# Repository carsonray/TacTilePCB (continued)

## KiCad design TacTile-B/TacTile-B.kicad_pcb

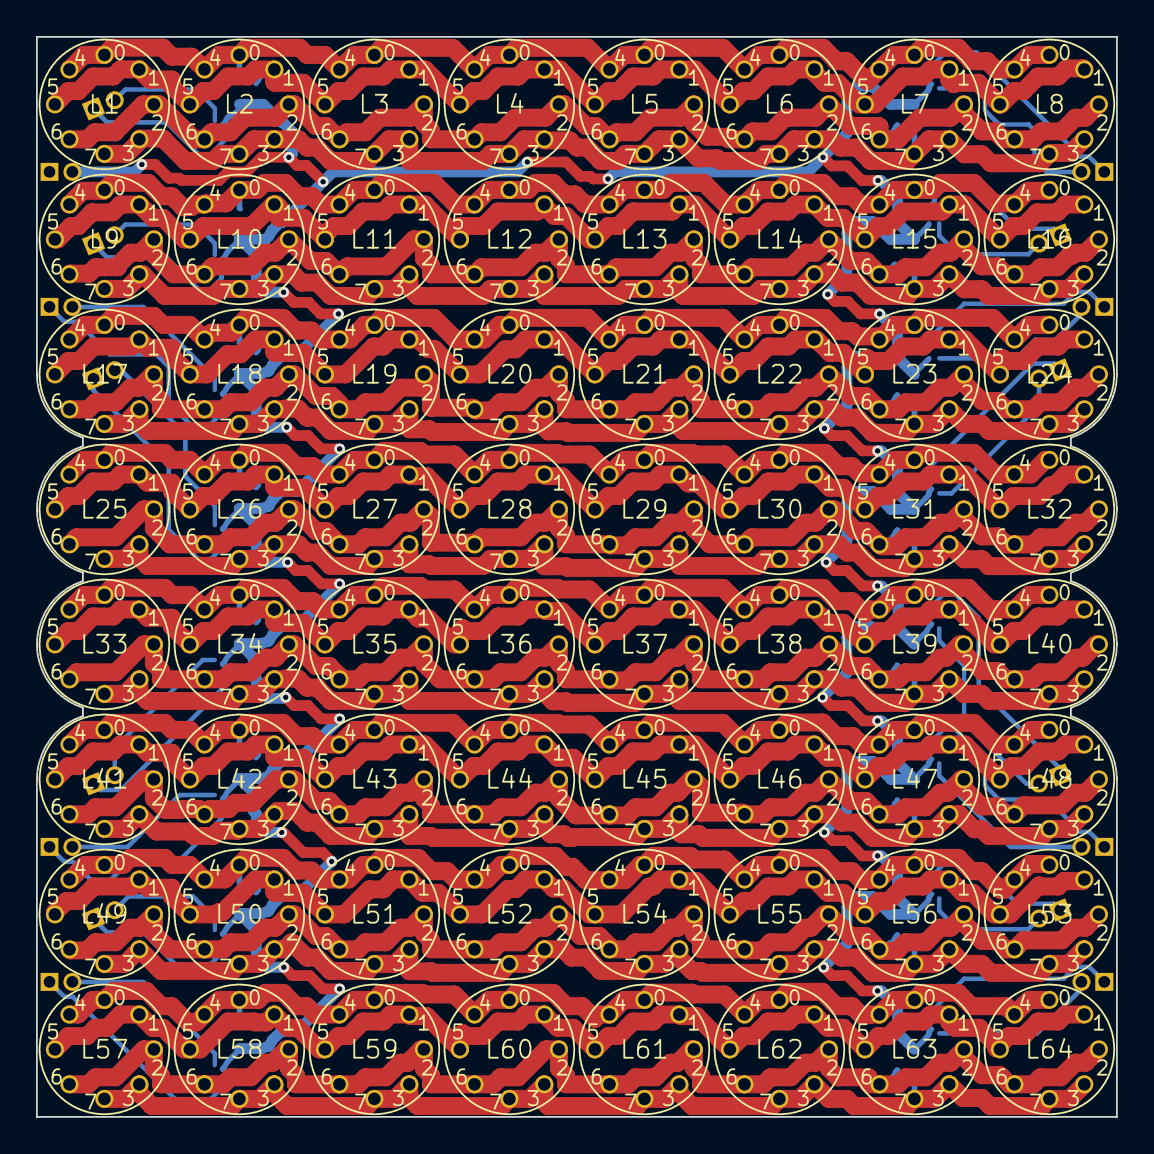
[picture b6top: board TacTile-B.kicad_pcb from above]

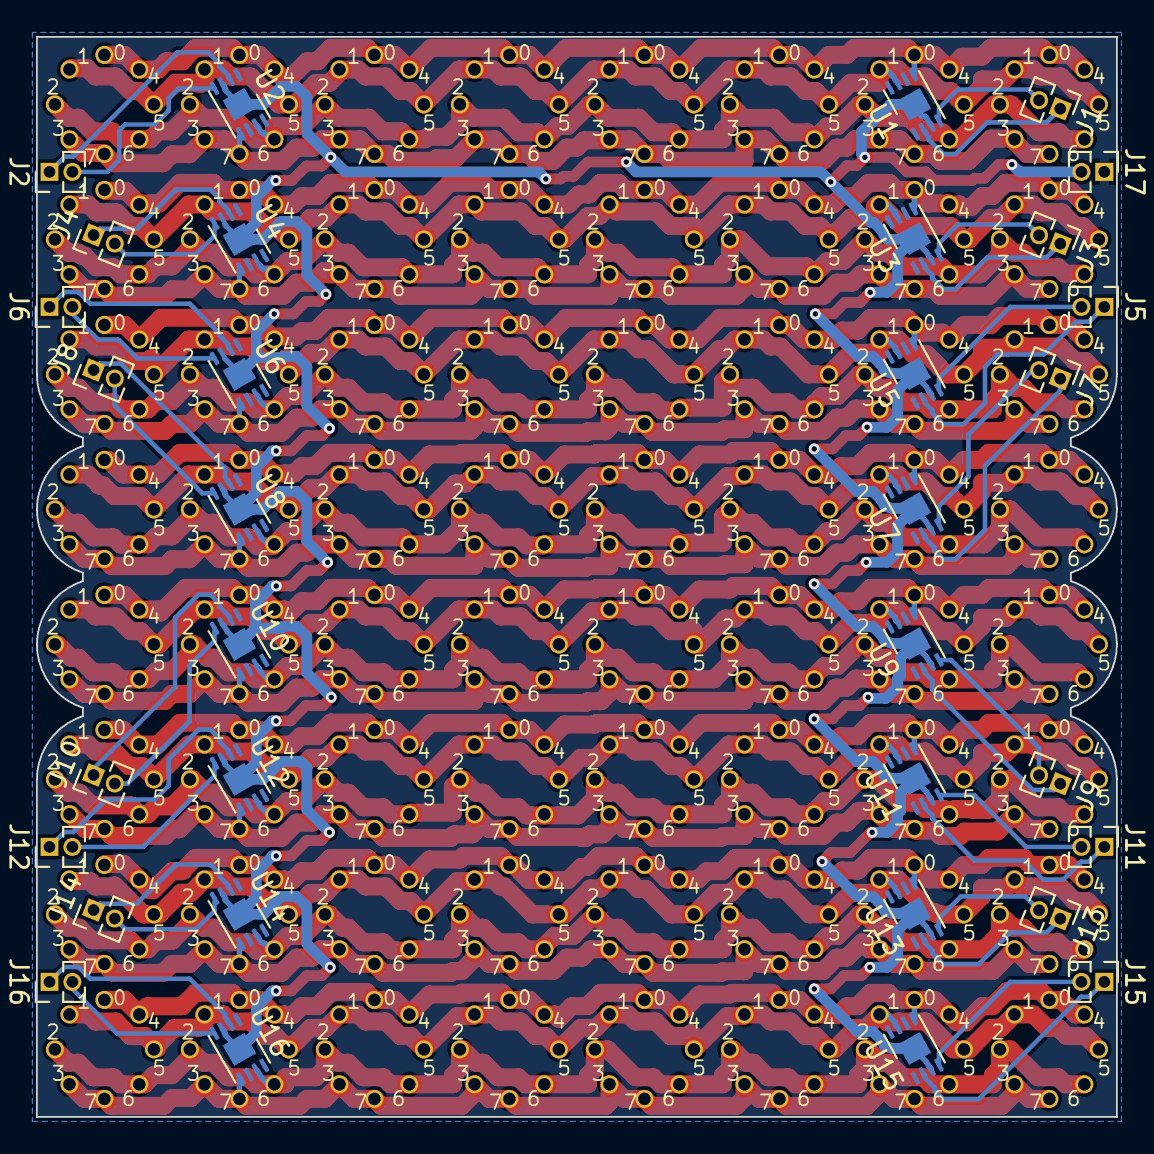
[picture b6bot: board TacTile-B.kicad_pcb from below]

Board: 2 copper layers, 60.0 x 60.0 mm, 97 parts (33 on the bottom side), 66 nets.

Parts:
J1, J2, J3, J4, J5, J6, J7, J8, J9, J10, J11, J12, J13, J14, J15, J16, J17: Conn_01x02; PinHeader_1x02_P1.27mm_Vertical
L1, L2, L3, L4, L5, L6, L7, L8, L9, L10, L11, L12, L13, L14, L15, L16, L17, L18, L19, L20, L21, L22, L23, L24, L25, L26, L27, L28, L29, L30, L31, L32, L33, L34, L35, L36, L37, L38, L39, L40, L41, L42, L43, L44, L45, L46, L47, L48, L49, L50, L51, L52, L53, L54, L55, L56, L57, L58, L59, L60, L61, L62, L63, L64: 8_coil_solenoid; 8_coil_solenoid_SMD
U1, U2, U3, U4, U5, U6, U7, U8, U9, U10, U11, U12, U13, U14, U15, U16: MCP14A0304xMNY; WDFN-8-1EP_3x2mm_P0.5mm_EP1.3x1.4mm

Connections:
/GND: J17.2, U1.3 (GND), U1.9 (GND), U2.3 (GND), U2.9 (GND), U3.3 (GND), U3.9 (GND), U4.3 (GND), U4.9 (GND), U5.3 (GND), U5.9 (GND), U6.3 (GND), U6.9 (GND), U7.3 (GND), U7.9 (GND), U8.3 (GND), U8.9 (GND), U9.3 (GND), U9.9 (GND), U10.3 (GND), U10.9 (GND), U11.3 (GND), U11.9 (GND), U12.3 (GND), U12.9 (GND), U13.3 (GND), U13.9 (GND), U14.3 (GND), U14.9 (GND), U15.3 (GND), U15.9 (GND), U16.3 (GND), U16.9 (GND)
/INP0: J1.2, U1.4 (INB)
/INP1: J1.1, U1.2 (INA)
/INP2: J2.1, U2.2 (INA)
/INP3: J2.2, U2.4 (INB)
/INP4: J3.2, U3.4 (INB)
/INP5: J3.1, U3.2 (INA)
/INP6: J4.1, U4.2 (INA)
/INP7: J4.2, U4.4 (INB)
/INP8: J5.2, U5.4 (INB)
/INP9: J5.1, U5.2 (INA)
/INP10: J6.1, U6.2 (INA)
/INP11: J6.2, U6.4 (INB)
/INP12: J7.2, U7.4 (INB)
/INP13: J7.1, U7.2 (INA)
/INP14: J8.1, U8.2 (INA)
/INP15: J8.2, U8.4 (INB)
/INP16: J9.2, U9.4 (INB)
/INP17: J9.1, U9.2 (INA)
/INP18: J10.1, U10.2 (INA)
/INP19: J10.2, U10.4 (INB)
/INP20: J11.2, U11.4 (INB)
/INP21: J11.1, U11.2 (INA)
/INP22: J12.1, U12.2 (INA)
/INP23: J12.2, U12.4 (INB)
/INP24: J13.2, U13.4 (INB)
/INP25: J13.1, U13.2 (INA)
/INP26: J14.1, U14.2 (INA)
/INP27: J14.2, U14.4 (INB)
/INP28: J15.2, U15.4 (INB)
/INP29: J15.1, U15.2 (INA)
/INP30: J16.1, U16.2 (INA)
/INP31: J16.2, U16.4 (INB)
/VIN: J17.1, U1.6 (V+), U2.6 (V+), U3.6 (V+), U4.6 (V+), U5.6 (V+), U6.6 (V+), U7.6 (V+), U8.6 (V+), U9.6 (V+), U10.6 (V+), U11.6 (V+), U12.6 (V+), U13.6 (V+), U14.6 (V+), U15.6 (V+), U16.6 (V+)
/VIN0: L1.1 (A), L1.5 (A), L2.1 (A), L2.5 (A), L3.1 (A), L3.5 (A), L4.1 (A), L4.5 (A), L5.1 (A), L5.5 (A), L6.1 (A), L6.5 (A), L7.1 (A), L7.5 (A), L8.1 (A), L8.5 (A), U1.5 (OUTB)
/VIN1: L1.2 (A), L1.6 (A), L2.2 (A), L2.6 (A), L3.2 (A), L3.6 (A), L4.2 (A), L4.6 (A), L5.2 (A), L5.6 (A), L6.2 (A), L6.6 (A), L7.2 (A), L7.6 (A), L8.2 (A), L8.6 (A), U1.7 (OUTA)
/VIN2: L1.3 (A), L1.7 (A), L2.3 (A), L2.7 (A), L3.3 (A), L3.7 (A), L4.3 (A), L4.7 (A), L5.3 (A), L5.7 (A), L6.3 (A), L6.7 (A), L7.3 (A), L7.7 (A), L8.3 (A), L8.7 (A), U2.7 (OUTA)
/VIN3: L1.4 (A), L1.8 (A), L2.4 (A), L2.8 (A), L3.4 (A), L3.8 (A), L4.4 (A), L4.8 (A), L5.4 (A), L5.8 (A), L6.4 (A), L6.8 (A), L7.4 (A), L7.8 (A), L8.4 (A), L8.8 (A), U2.5 (OUTB)
/VIN4: L9.1 (A), L9.5 (A), L10.1 (A), L10.5 (A), L11.1 (A), L11.5 (A), L12.1 (A), L12.5 (A), L13.1 (A), L13.5 (A), L14.1 (A), L14.5 (A), L15.1 (A), L15.5 (A), L16.1 (A), L16.5 (A), U3.5 (OUTB)
/VIN5: L9.2 (A), L9.6 (A), L10.2 (A), L10.6 (A), L11.2 (A), L11.6 (A), L12.2 (A), L12.6 (A), L13.2 (A), L13.6 (A), L14.2 (A), L14.6 (A), L15.2 (A), L15.6 (A), L16.2 (A), L16.6 (A), U3.7 (OUTA)
/VIN6: L9.3 (A), L9.7 (A), L10.3 (A), L10.7 (A), L11.3 (A), L11.7 (A), L12.3 (A), L12.7 (A), L13.3 (A), L13.7 (A), L14.3 (A), L14.7 (A), L15.3 (A), L15.7 (A), L16.3 (A), L16.7 (A), U4.7 (OUTA)
/VIN7: L9.4 (A), L9.8 (A), L10.4 (A), L10.8 (A), L11.4 (A), L11.8 (A), L12.4 (A), L12.8 (A), L13.4 (A), L13.8 (A), L14.4 (A), L14.8 (A), L15.4 (A), L15.8 (A), L16.4 (A), L16.8 (A), U4.5 (OUTB)
/VIN8: L17.1 (A), L17.5 (A), L18.1 (A), L18.5 (A), L19.1 (A), L19.5 (A), L20.1 (A), L20.5 (A), L21.1 (A), L21.5 (A), L22.1 (A), L22.5 (A), L23.1 (A), L23.5 (A), L24.1 (A), L24.5 (A), U5.5 (OUTB)
/VIN9: L17.2 (A), L17.6 (A), L18.2 (A), L18.6 (A), L19.2 (A), L19.6 (A), L20.2 (A), L20.6 (A), L21.2 (A), L21.6 (A), L22.2 (A), L22.6 (A), L23.2 (A), L23.6 (A), L24.2 (A), L24.6 (A), U5.7 (OUTA)
/VIN10: L17.3 (A), L17.7 (A), L18.3 (A), L18.7 (A), L19.3 (A), L19.7 (A), L20.3 (A), L20.7 (A), L21.3 (A), L21.7 (A), L22.3 (A), L22.7 (A), L23.3 (A), L23.7 (A), L24.3 (A), L24.7 (A), U6.7 (OUTA)
/VIN11: L17.4 (A), L17.8 (A), L18.4 (A), L18.8 (A), L19.4 (A), L19.8 (A), L20.4 (A), L20.8 (A), L21.4 (A), L21.8 (A), L22.4 (A), L22.8 (A), L23.4 (A), L23.8 (A), L24.4 (A), L24.8 (A), U6.5 (OUTB)
/VIN12: L25.1 (A), L25.5 (A), L26.1 (A), L26.5 (A), L27.1 (A), L27.5 (A), L28.1 (A), L28.5 (A), L29.1 (A), L29.5 (A), L30.1 (A), L30.5 (A), L31.1 (A), L31.5 (A), L32.1 (A), L32.5 (A), U7.5 (OUTB)
/VIN13: L25.2 (A), L25.6 (A), L26.2 (A), L26.6 (A), L27.2 (A), L27.6 (A), L28.2 (A), L28.6 (A), L29.2 (A), L29.6 (A), L30.2 (A), L30.6 (A), L31.2 (A), L31.6 (A), L32.2 (A), L32.6 (A), U7.7 (OUTA)
/VIN14: L25.3 (A), L25.7 (A), L26.3 (A), L26.7 (A), L27.3 (A), L27.7 (A), L28.3 (A), L28.7 (A), L29.3 (A), L29.7 (A), L30.3 (A), L30.7 (A), L31.3 (A), L31.7 (A), L32.3 (A), L32.7 (A), U8.7 (OUTA)
/VIN15: L25.4 (A), L25.8 (A), L26.4 (A), L26.8 (A), L27.4 (A), L27.8 (A), L28.4 (A), L28.8 (A), L29.4 (A), L29.8 (A), L30.4 (A), L30.8 (A), L31.4 (A), L31.8 (A), L32.4 (A), L32.8 (A), U8.5 (OUTB)
/VIN16: L33.1 (A), L33.5 (A), L34.1 (A), L34.5 (A), L35.1 (A), L35.5 (A), L36.1 (A), L36.5 (A), L37.1 (A), L37.5 (A), L38.1 (A), L38.5 (A), L39.1 (A), L39.5 (A), L40.1 (A), L40.5 (A), U9.5 (OUTB)
/VIN17: L33.2 (A), L33.6 (A), L34.2 (A), L34.6 (A), L35.2 (A), L35.6 (A), L36.2 (A), L36.6 (A), L37.2 (A), L37.6 (A), L38.2 (A), L38.6 (A), L39.2 (A), L39.6 (A), L40.2 (A), L40.6 (A), U9.7 (OUTA)
/VIN18: L33.3 (A), L33.7 (A), L34.3 (A), L34.7 (A), L35.3 (A), L35.7 (A), L36.3 (A), L36.7 (A), L37.3 (A), L37.7 (A), L38.3 (A), L38.7 (A), L39.3 (A), L39.7 (A), L40.3 (A), L40.7 (A), U10.7 (OUTA)
/VIN19: L33.4 (A), L33.8 (A), L34.4 (A), L34.8 (A), L35.4 (A), L35.8 (A), L36.4 (A), L36.8 (A), L37.4 (A), L37.8 (A), L38.4 (A), L38.8 (A), L39.4 (A), L39.8 (A), L40.4 (A), L40.8 (A), U10.5 (OUTB)
/VIN20: L41.1 (A), L41.5 (A), L42.1 (A), L42.5 (A), L43.1 (A), L43.5 (A), L44.1 (A), L44.5 (A), L45.1 (A), L45.5 (A), L46.1 (A), L46.5 (A), L47.1 (A), L47.5 (A), L48.1 (A), L48.5 (A), U11.5 (OUTB)
/VIN21: L41.2 (A), L41.6 (A), L42.2 (A), L42.6 (A), L43.2 (A), L43.6 (A), L44.2 (A), L44.6 (A), L45.2 (A), L45.6 (A), L46.2 (A), L46.6 (A), L47.2 (A), L47.6 (A), L48.2 (A), L48.6 (A), U11.7 (OUTA)
/VIN22: L41.3 (A), L41.7 (A), L42.3 (A), L42.7 (A), L43.3 (A), L43.7 (A), L44.3 (A), L44.7 (A), L45.3 (A), L45.7 (A), L46.3 (A), L46.7 (A), L47.3 (A), L47.7 (A), L48.3 (A), L48.7 (A), U12.7 (OUTA)
/VIN23: L41.4 (A), L41.8 (A), L42.4 (A), L42.8 (A), L43.4 (A), L43.8 (A), L44.4 (A), L44.8 (A), L45.4 (A), L45.8 (A), L46.4 (A), L46.8 (A), L47.4 (A), L47.8 (A), L48.4 (A), L48.8 (A), U12.5 (OUTB)
/VIN24: L49.1 (A), L49.5 (A), L50.1 (A), L50.5 (A), L51.1 (A), L51.5 (A), L52.1 (A), L52.5 (A), L53.1 (A), L53.5 (A), L54.1 (A), L54.5 (A), L55.1 (A), L55.5 (A), L56.1 (A), L56.5 (A), U13.5 (OUTB)
/VIN25: L49.2 (A), L49.6 (A), L50.2 (A), L50.6 (A), L51.2 (A), L51.6 (A), L52.2 (A), L52.6 (A), L53.2 (A), L53.6 (A), L54.2 (A), L54.6 (A), L55.2 (A), L55.6 (A), L56.2 (A), L56.6 (A), U13.7 (OUTA)
/VIN26: L49.3 (A), L49.7 (A), L50.3 (A), L50.7 (A), L51.3 (A), L51.7 (A), L52.3 (A), L52.7 (A), L53.3 (A), L53.7 (A), L54.3 (A), L54.7 (A), L55.3 (A), L55.7 (A), L56.3 (A), L56.7 (A), U14.7 (OUTA)
/VIN27: L49.4 (A), L49.8 (A), L50.4 (A), L50.8 (A), L51.4 (A), L51.8 (A), L52.4 (A), L52.8 (A), L53.4 (A), L53.8 (A), L54.4 (A), L54.8 (A), L55.4 (A), L55.8 (A), L56.4 (A), L56.8 (A), U14.5 (OUTB)
/VIN28: L57.1 (A), L57.5 (A), L58.1 (A), L58.5 (A), L59.1 (A), L59.5 (A), L60.1 (A), L60.5 (A), L61.1 (A), L61.5 (A), L62.1 (A), L62.5 (A), L63.1 (A), L63.5 (A), L64.1 (A), L64.5 (A), U15.5 (OUTB)
/VIN29: L57.2 (A), L57.6 (A), L58.2 (A), L58.6 (A), L59.2 (A), L59.6 (A), L60.2 (A), L60.6 (A), L61.2 (A), L61.6 (A), L62.2 (A), L62.6 (A), L63.2 (A), L63.6 (A), L64.2 (A), L64.6 (A), U15.7 (OUTA)
/VIN30: L57.3 (A), L57.7 (A), L58.3 (A), L58.7 (A), L59.3 (A), L59.7 (A), L60.3 (A), L60.7 (A), L61.3 (A), L61.7 (A), L62.3 (A), L62.7 (A), L63.3 (A), L63.7 (A), L64.3 (A), L64.7 (A), U16.7 (OUTA)
/VIN31: L57.4 (A), L57.8 (A), L58.4 (A), L58.8 (A), L59.4 (A), L59.8 (A), L60.4 (A), L60.8 (A), L61.4 (A), L61.8 (A), L62.4 (A), L62.8 (A), L63.4 (A), L63.8 (A), L64.4 (A), L64.8 (A), U16.5 (OUTB)

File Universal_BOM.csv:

#,Board,Reference,Qty,Value,Footprint,DNP
1,A,"J1, J3",2,Conn_01x01,Connector_PinSocket_2.54mm:PinSocket_1x01_P2.54mm_Horizontal,
2,A,"J2, J4",2,Conn_01x01,Connector_PinHeader_2.54mm:PinHeader_1x01_P2.54mm_Horizontal,
3,A,"JMP1, JMP2, JMP3, JMP4, JMP5, JMP6, JMP7, JMP8, JMP9, JMP10, JMP11, JMP12, JMP13, JMP14, JMP15, JMP16",16,~,TacTile:Jumper_Connect,
4,A,"L1, L2, L3, L4, L5, L6, L7, L8, L9, L10, L11, L12, L13, L14, L15, L16, L17, L18, L19, L20, L21, L22, L23, L24, L25, L26, L27, L28, L29, L30, L31, L32, L33, L34, L35, L36, L37, L38, L39, L40, L41, L42, L43, L44, L45, L46, L47, L48, L49, L50, L51, L52, L53, L54, L55, L56, L57, L58, L59, L60, L61, L62, L63, L64",64,8_coil_solenoid,TacTile:8_coil_solenoid,
5,A,"U1, U2, U3, U4, U5, U6, U7, U8, U9, U10, U11, U12, U13, U14, U15, U16",16,MCP14A0304xMNY,Package_DFN_QFN:WDFN-8-1EP_3x2mm_P0.5mm_EP1.3x1.4mm,
6,B,"J1, J2, J3, J4, J5, J6, J7, J8, J9, J10, J11, J12, J13, J14, J15, J16, J17",17,Conn_01x02,Connector_PinHeader_1.27mm:PinHeader_1x02_P1.27mm_Vertical,
7,B,"L1, L2, L3, L4, L5, L6, L7, L8, L9, L10, L11, L12, L13, L14, L15, L16, L17, L18, L19, L20, L21, L22, L23, L24, L25, L26, L27, L28, L29, L30, L31, L32, L33, L34, L35, L36, L37, L38, L39, L40, L41, L42, L43, L44, L45, L46, L47, L48, L49, L50, L51, L52, L53, L54, L55, L56, L57, L58, L59, L60, L61, L62, L63, L64",64,8_coil_solenoid,TacTile:8_coil_solenoid_SMD,
8,B,"U1, U2, U3, U4, U5, U6, U7, U8, U9, U10, U11, U12, U13, U14, U15, U16",16,MCP14A0304xMNY,Package_DFN_QFN:WDFN-8-1EP_3x2mm_P0.5mm_EP1.3x1.4mm,
9,C,"J1, J2, J3, J4, J5, J6, J7, J8, J9, J10, J11, J12, J13, J14, J15, J16, J17",17,Conn_01x02,Connector_PinSocket_1.27mm:PinSocket_1x02_P1.27mm_Vertical,
10,C,J18,1,Conn_01x04,Connector_PinHeader_2.54mm:PinHeader_1x04_P2.54mm_Vertical,
11,C,J19,1,Conn_01x05,Connector_PinHeader_2.54mm:PinHeader_1x05_P2.54mm_Vertical,
12,C,"J20, J21",2,Conn_01x02,Connector_PinHeader_2.54mm:PinHeader_1x02_P2.54mm_Vertical,
13,C,"JMP1, JMP2, JMP3, JMP4, JMP5, JMP6, JMP7, JMP8, JMP9, JMP10, JMP11, JMP12, JMP13, JMP14, JMP15, JMP16",16,~,TacTile:Jumper_Connect,
14,C,"U1, U2, U3, U4, U5, U6, U7, U8",8,74HC4051,Package_DIP:DIP-16_W7.62mm,
15,D,"J1, J2",2,Conn_01x06,Connector_PinSocket_2.54mm:PinSocket_1x06_P2.54mm_Horizontal,
16,D,"J3, J4",2,Conn_01x06,Connector_PinHeader_2.54mm:PinHeader_1x06_P2.54mm_Horizontal,
17,D,J5,1,Conn_01x04,Connector_PinSocket_2.54mm:PinSocket_1x04_P2.54mm_Vertical,
18,D,J6,1,Conn_01x05,Connector_PinSocket_2.54mm:PinSocket_1x05_P2.54mm_Vertical,
19,D,"J7, J8",2,Conn_01x02,Connector_PinSocket_2.54mm:PinSocket_1x02_P2.54mm_Vertical,
20,D,U1,1,74LS04,Package_DIP:DIP-14_W7.62mm,
21,D,U2,1,4011,Package_DIP:DIP-14_W7.62mm,
22,D,U3,1,74HC595,Package_DIP:DIP-16_W7.62mm,
23,D,U4,1,74HC590,Package_DIP:DIP-16_W7.62mm,
24,D,"U5, U7",2,74LS74,Package_DIP:DIP-14_W7.62mm,
25,D,U6,1,74HC08,Package_DIP:DIP-14_W7.62mm,
26,D,U8,1,4042,Package_DIP:DIP-16_W7.62mm,
27,D,U9,1,74HC4051,Package_DIP:DIP-16_W7.62mm,
28,L1,J1,1,Conn_01x02,Connector_PinSocket_2.54mm:PinSocket_1x02_P2.54mm_Horizontal,
29,L1,J2,1,Conn_01x02,Connector_PinHeader_2.54mm:PinHeader_1x02_P2.54mm_Horizontal,
30,L1,"LD1, LD2, LD3, LD4, LD5, LD6, LD7, LD8",8,D_Laser_1C2A,TacTile:Laser_Diode,
31,L1C,J1,1,Conn_01x02,Connector_PinSocket_2.54mm:PinSocket_1x02_P2.54mm_Horizontal,
32,L1C,J2,1,Conn_01x02,Connector_PinHeader_2.54mm:PinHeader_1x02_P2.54mm_Horizontal,
33,L2,J1,1,Conn_01x05,Connector_PinSocket_2.54mm:PinSocket_1x05_P2.54mm_Horizontal,
34,L2,J2,1,Conn_01x05,Connector_PinHeader_2.54mm:PinHeader_1x05_P2.54mm_Horizontal,
35,L2,"R1, R2, R3, R4, R5, R6, R7, R8",8,R_Photo,TacTile:Photoresistor,
36,L2,U1,1,74HC595,Package_DIP:DIP-16_W7.62mm,
37,L2C,J1,1,Conn_01x05,Connector_PinSocket_2.54mm:PinSocket_1x05_P2.54mm_Horizontal,
38,L2C,J2,1,Conn_01x05,Connector_PinHeader_2.54mm:PinHeader_1x05_P2.54mm_Horizontal,

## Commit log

2023-08-11 Began layout and routing of board C
2023-08-12 Finished board C layout
2023-08-12 Selected and placed footprints for board D
2023-08-12 Made board D layout more efficient
2023-08-12 Wired board D power traces
2023-08-13 Began routing Board D
2023-08-13 Finished board D routing
2023-08-14 Added STEP files
2023-08-14 Generated fabrication files
2023-08-23 Ensured outputs were disabled on reset - added not gate
2023-08-23 Mounted ICs without sockets to save space
2023-08-23 Enlarged solenoid pads to fit connector pins
2023-08-23 Added schematics for laser grid boards
2023-08-24 Added some footprints for laser boards
2023-08-28 Added photoresistor footprint and enlarged main boards to 60mm
2023-08-29 Finished L2 Board
2023-08-29 Finished L1 Board
2023-08-29 Swapped headers and sockets on board A
2023-08-29 Enlarged B-C interface to 2.54 pitch connectors
2023-08-29 Enlarged connectors on board D to 2.54mm pitch
2023-08-30 Finished rewiring board D
2023-08-30 Finished enlarging pins on C, D, L1, L2
2023-08-30 Created connector boards for laser matrix
2023-08-30 Updated fabrication and STEP files
2023-08-30 Enlarged grounding pins on board A
2023-08-31 Used 16DIP demultiplexer instead of single demultiplexer
2023-09-07 Updated D schematic to reflect available ICs
2023-09-07 Checked new board D spacing requirements
2023-09-14 Finished layout with new ICs on board D
2023-09-23 Adjusted mounting for laser boards
2023-10-04 Finalized fabrication outputs and fixed repeated layers
2023-10-09 Updated more fabrication files and D board selecting wrong coil
2023-12-27 Redid A board with MOSFETs sinking current
2023-12-28 Added voltage input to A MOSFETs
2023-12-31 Fixed issues with D board and rerouted
2024-01-11 Exported new fab files
2024-01-11 Fixed counter clocking delay on D board
2024-01-11 Exported new fabrication files
2024-04-10 Fixed some numberings
